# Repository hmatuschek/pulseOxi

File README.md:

# A USB pulse oximeter 

An pulse oximeter is a relatively simple device. It uses the property of hemoglobin to change its absorption spectrum around 660nm (red) and to some lesser degree around 940nm (infrared) when saturated with oxygen. This change in the absorption spectrum can therefore be measured indirectly by measuring the amount (intensity, brightness) of red and infrared light being transmitted through or back-scattered from e.g. a finger. 

The absolute amount of light that gets detected, however, depends on many factors, including the sensitivity of the detector (photo diode), the light source (LEDs), how the detector and sources are fixated on the skin and, of course, on physiognomic properties of the finger. These dependencies turn the measurement with a single light source virtually impossible. Many of these influences, however, affect light of all wavelengths. Hence it is possible to reduce these influences on the measurement by measuring the brightness of light of more than one wavelength. The oxidation of hemoglobin changes its absorption at different wavelengths differently, hence using two light sources with different wavelengths allows to cancel out the influences which are wavelength insensitive. This "trick" then allows to measure the oxidation of the hemoglobin by measuring the change in the difference of the intensities at these two wavelengths. 

## The hardware

For the [circuit](https://github.com/hmatuschek/pulseOxi/blob/master/hardware/pulse_scm.pdf), two LEDs are used as light sources. One red led (around 645nm) and one infra red (IR, 900nm) led. The intensity of the transmitted light is then measured using a photo diode. The current through this diode is then converted to a voltage using a operational amplifier (opamp). The voltage signal is then sampled using one of the analog/digital converters (ADCs) of the ATtiny45. By switching the LEDs on and off (also controlled by the ATtiny), the intensity difference can be computed, representing the relative oxidation level of the hemoglobin. For more details on how to construct a pulse-oximeter, consider the [AN4327 application node](http://www.nxp.com/files/32bit/doc/app_note/AN4327.pdf) by NXP. 

This circuit is very reduced. It was designed as a USB dongle without using SMD parts. Hence many parts usually enhancing the circuit stability and reliability have been omitted and should be added when a larger form factor is chosen. For example, I omitted:

  * LED driver circuits,
  * A proper blocking pi-network or even a larger blocking capacitor to stabilize the supply voltage, 
  * A small capacitor in parallel to the feed-back resistor of the transimpedance amplifier,
  * A proper reference voltage for the transimpedance amplifier.

Given the simplicity of the circuit, the results are surprisingly good. 

Please note that the LEDs are driven directly by the digital outputs of the ATtiny. They are able to deliver (only) about 20-30mA. Hence choose the LEDs and their series resistors accordingly. The circuit above does not include the series resistors. They are connected directly to the LEDs at the clip. The single LEDs are driven by ATtiny in a H-bridge way. That is, one of the LED pins acts as a source and one as a sink. This allows to drive the LEDs with two wires only but does not allow for driving them both simultaneously. Hence the LEDs must be connected to the ATtiny like shown in the circuit above.

## The client software

The client software provides a convenient [Qt5](https://qt.io) GUI application using [QCustomPlot](http://www.qcustomplot.com/) for potting and [libusb](http://libusb.info/) to interface the pulse oximeter hardware.

The upper half shows the (approx.) SpO2 level (relative oxygen saturation, blue line) together with an estimate of the pulse rate in BPM (red line). The smaller bottom plot shows the pulse signal obtained for the IR channel (blue line) and red channel (red line) from which the pulse rate gets estimated. With the current implementation, the baseline and AC signal (deviance from the baseline) as well as the amplitude of the AC signal are obtained using sinc-convolution filters. This implies a short delay (about 5s) between the actual measurement and the display.

## Features

 * Small circuit.
 * USB interface using [V-USB](https://www.obdev.at/products/vusb/index-de.html).
 * USB powered.

## License
Pulse - A simple pulse oximeter. (c) 2015 Hannes Matuschek <hmatuschek at gmail dot com>

The hardware is licensed under [Createtive Commons BY-SA 4.0](https://creativecommons.org/licenses/by-sa/4.0/) and the software under [GPL 2.0+](https://www.gnu.org/licenses/old-licenses/gpl-2.0.txt) (see below).

This program is free software; you can redistribute it and/or
modify it under the terms of the GNU General Public License
as published by the Free Software Foundation; either version 2
of the License, or (at your option) any later version.</p>

This program is distributed in the hope that it will be useful,
but WITHOUT ANY WARRANTY; without even the implied warranty of
MERCHANTABILITY or FITNESS FOR A PARTICULAR PURPOSE.  See the
GNU General Public License for more details.

You should have received a copy of the GNU General Public License
along with this program; if not, write to the Free Software
Foundation, Inc., 51 Franklin Street, Fifth Floor, Boston, MA  02110-1301, USA.

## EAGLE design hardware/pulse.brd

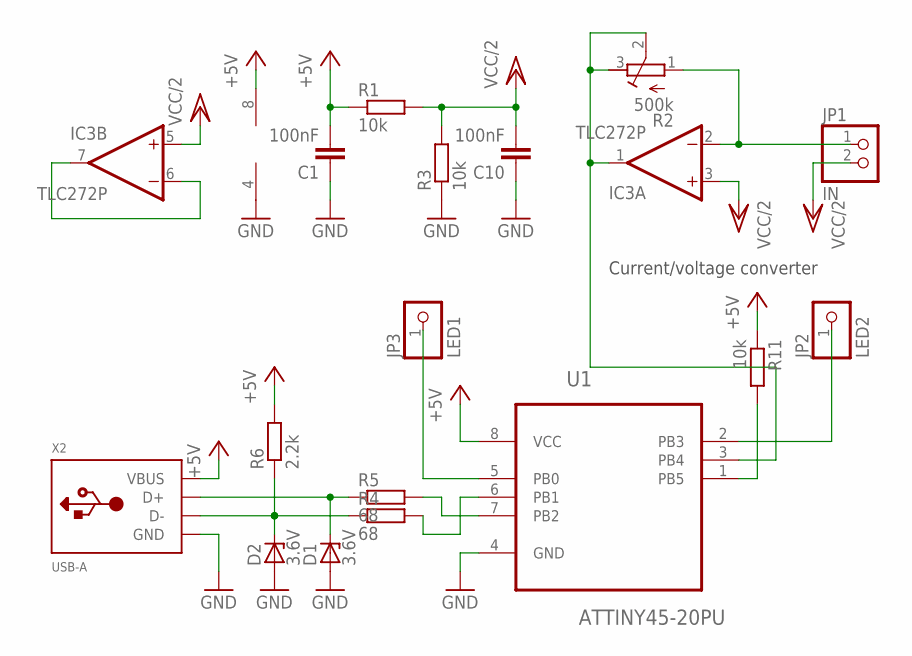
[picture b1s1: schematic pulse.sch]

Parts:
C1: 100nF; C075-032X103
C10: 100nF; C050-025X075
D1: 3.6V; ZDIO-2.5
D2: 3.6V; ZDIO-5
IC3: TLC272P; DIL08
JP1: IN; 1X02
JP2: LED2; 1X01
JP3: LED1; 1X01
R1: 10k; 0207/12
R2: 500k; RTRIM64W
R3: 10k; 0204V
R4, R5: 68; 0204V
R6: 2.2k; 0204V
R11: 10k; 0204/7
U1: ATTINY45-20PU; DIP254P762X533-8
X2: USB-A; MOLEX_480371000

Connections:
+5V: C1.2, IC3.8 (V+), R1.1, R6.2, R11.1, U1.8 (VCC), X2.1 (VBUS)
GND: C1.1, C10.1, D1.A, D2.A, IC3.4 (V-), R3.1, U1.4 (GND), X2.4 (GND)
unnamed: IC3.2 (-IN), JP1.1, R2.1 (A)
unnamed: R5.2, U1.7 (PB2)
unnamed: R4.2, U1.6 (PB1)
unnamed: JP2.1, U1.2 (PB3)
unnamed: JP3.1, U1.5 (PB0)
unnamed: IC3.6 (-IN), IC3.7 (OUT)
unnamed: IC3.1 (OUT), R2.2 (S), R2.3 (E), U1.3 (PB4)
unnamed: R11.2, U1.1 (PB5)
unnamed: D1.C, R5.1, X2.3 (D+)
unnamed: D2.C, R4.1, R6.1, X2.2 (D-)
VCC/2: C10.2, IC3.3 (+IN), IC3.5 (+IN), JP1.2, R1.2, R3.2

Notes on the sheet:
Current/voltage converter

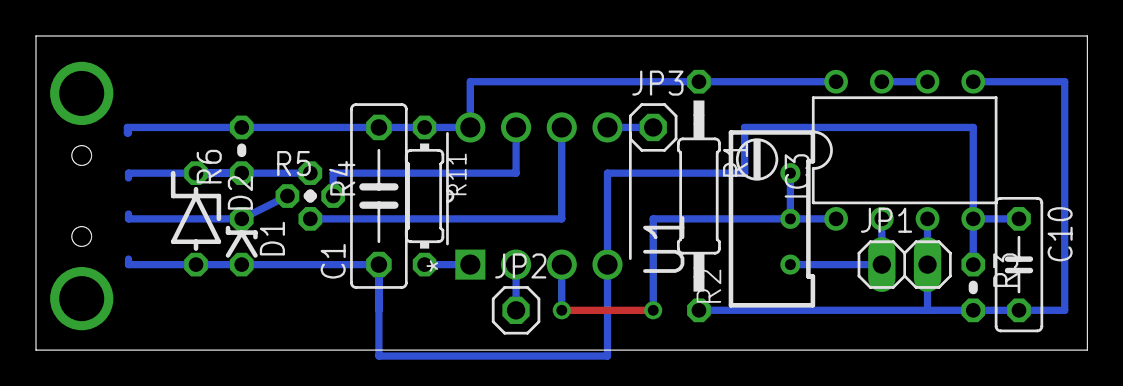
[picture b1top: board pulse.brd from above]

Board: 2 copper layers, 58.4 x 17.5 mm, 17 parts (1 on the bottom side), 13 nets.

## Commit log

2015-11-03 Initial.
2015-11-03 Added dirs.
2015-11-03 Added first version of the circuit.
2015-11-04 Fixed circuit and board.
2015-11-05 Added software basics.
2016-07-19 Rewritten to large parts.
2016-07-19 Fixed minors.
2016-07-23 Fixed firmware completed hardware.
2016-07-25 Added toolbar.
2016-07-25 Added schematic print.
2016-07-25 Fixed readme.
2016-07-25 Cleanup.
2016-07-25 Added LED circ.
2016-07-25 Oops.
2016-07-25 Added schematic to readme.
2016-07-25 Added screen shot.
2016-07-25 Fixed pulse detection & updated screen shot.
2016-07-25 Updated schematic & board.
2016-07-26 Updated V-USB driver & added RC calibration.
